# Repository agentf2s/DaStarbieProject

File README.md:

# DaStarbieProject
It is the repository of the starbie project for half life

*So why am I doing this?*

I participated in a 10 week challenge to build hardware and this is one of the starter projects. I wasn't sure what exactly I wanted to build so I went for the starter project. I'm required to have a repo containing everything so this is it.

*What is it?*

A tamagotchi style thing that responds to the way you move and the buttons you click.
It's super duper cool.

*How*

Use the PCB Designs uploaded, if you want to remake it then make sure you import the footprint library I've included. Get the pcb printed, and use arduino IDE to upload the firmware to the esp32. Should be simple enough.

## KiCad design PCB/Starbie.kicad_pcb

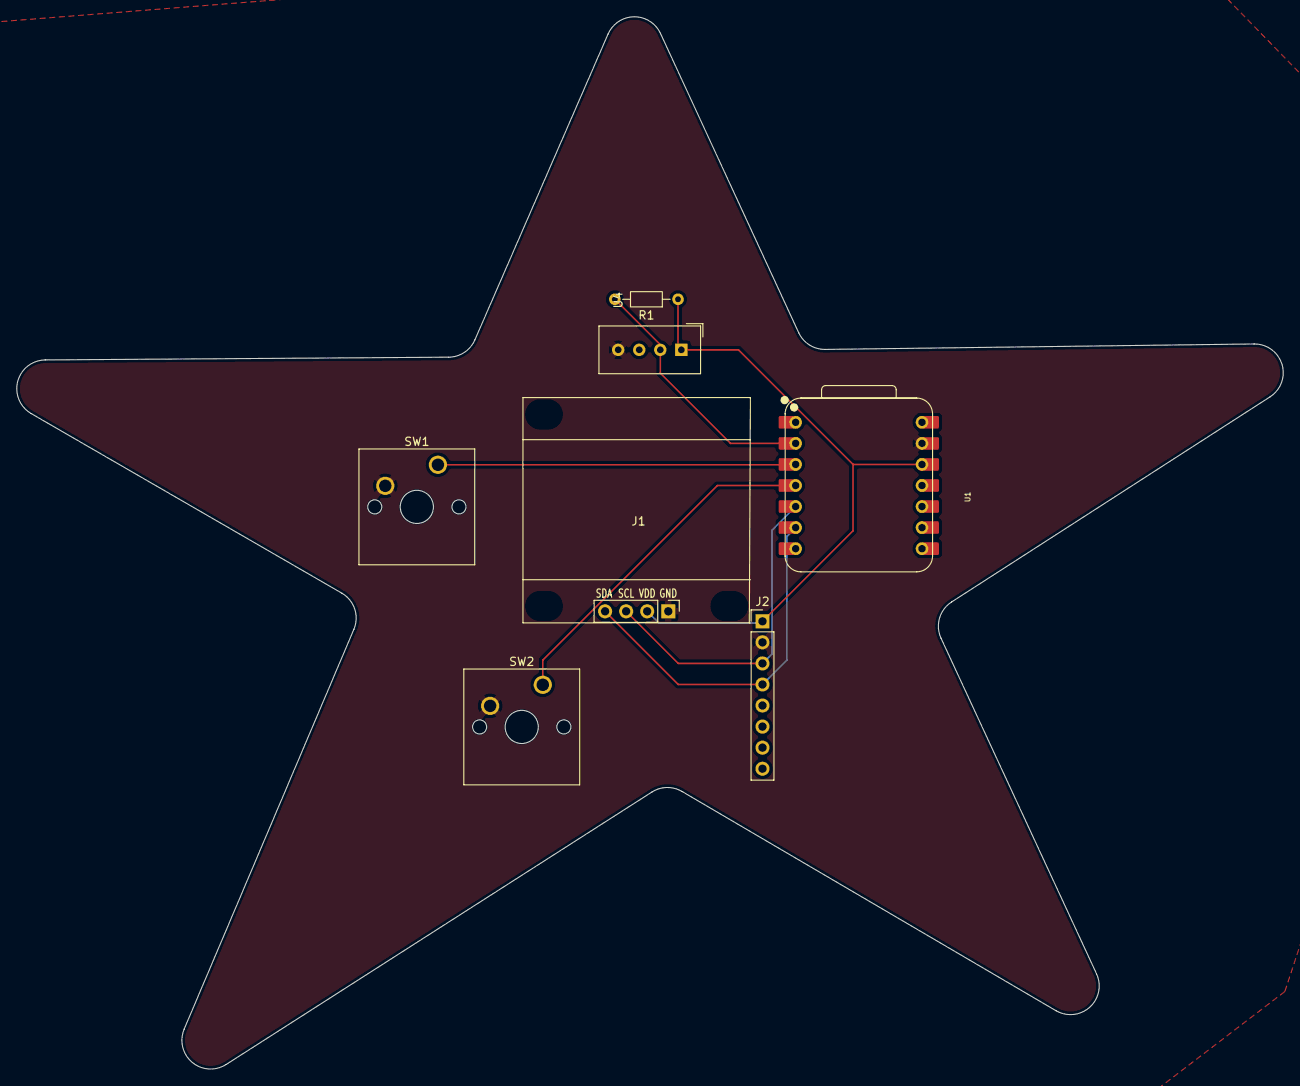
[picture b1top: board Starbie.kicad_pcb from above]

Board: 2 copper layers, 152.8 x 126.9 mm, 7 parts (0 on the bottom side), 7 nets.

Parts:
J1: Conn_01x04_Pin; Display_128x64_096_I2C
J2: Conn_01x08_Pin; PinHeader_1x08_P2.54mm_Vertical
R1: R; R_Axial_DIN0204_L3.6mm_D1.6mm_P7.62mm_Horizontal
SW1, SW2: SW_Push; SW_Cherry_MX_1.00u_PCB
U1: XIAO-ESP32-C3-SMD; XIAO-ESP32-C6-DIP
U4: DHT11; Aosong_DHT11_5.5x12.0_P2.54mm

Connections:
+3.3V: J1.2, J2.1, R1.1, U1.12 (3V3_OUT), U4.1 (VDD)
/DHT11 DATA: R1.2, U1.2 (D1), U4.2 (DATA)
/GPIO2: SW1.1, U1.3 (D2)
/GPIO3: SW2.1, U1.4 (D3)
/SCL: J1.3, J2.3, U1.5 (D4)
/SDA: J1.4, J2.4, U1.6 (D5)
GND: J1.1, J2.2, SW1.2, SW2.2, U1.13 (GND), U4.4 (GND)
